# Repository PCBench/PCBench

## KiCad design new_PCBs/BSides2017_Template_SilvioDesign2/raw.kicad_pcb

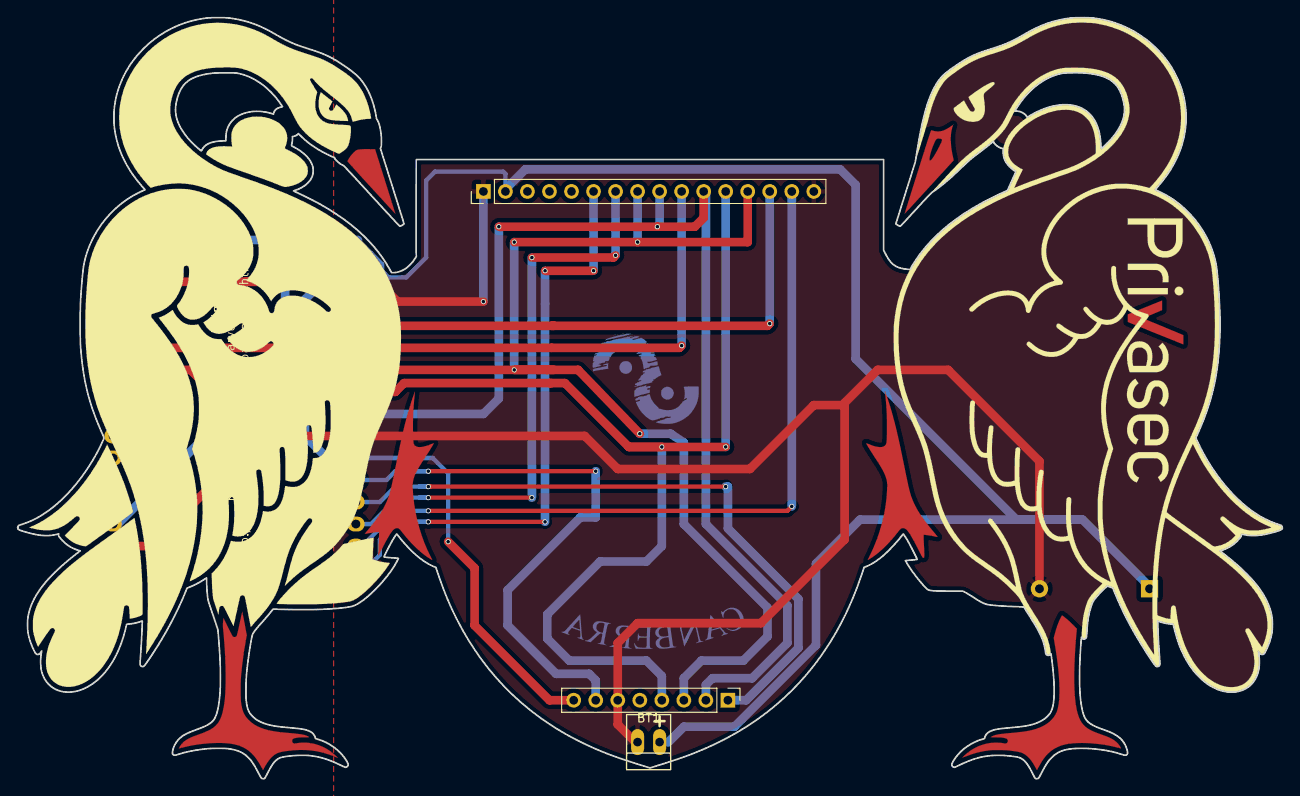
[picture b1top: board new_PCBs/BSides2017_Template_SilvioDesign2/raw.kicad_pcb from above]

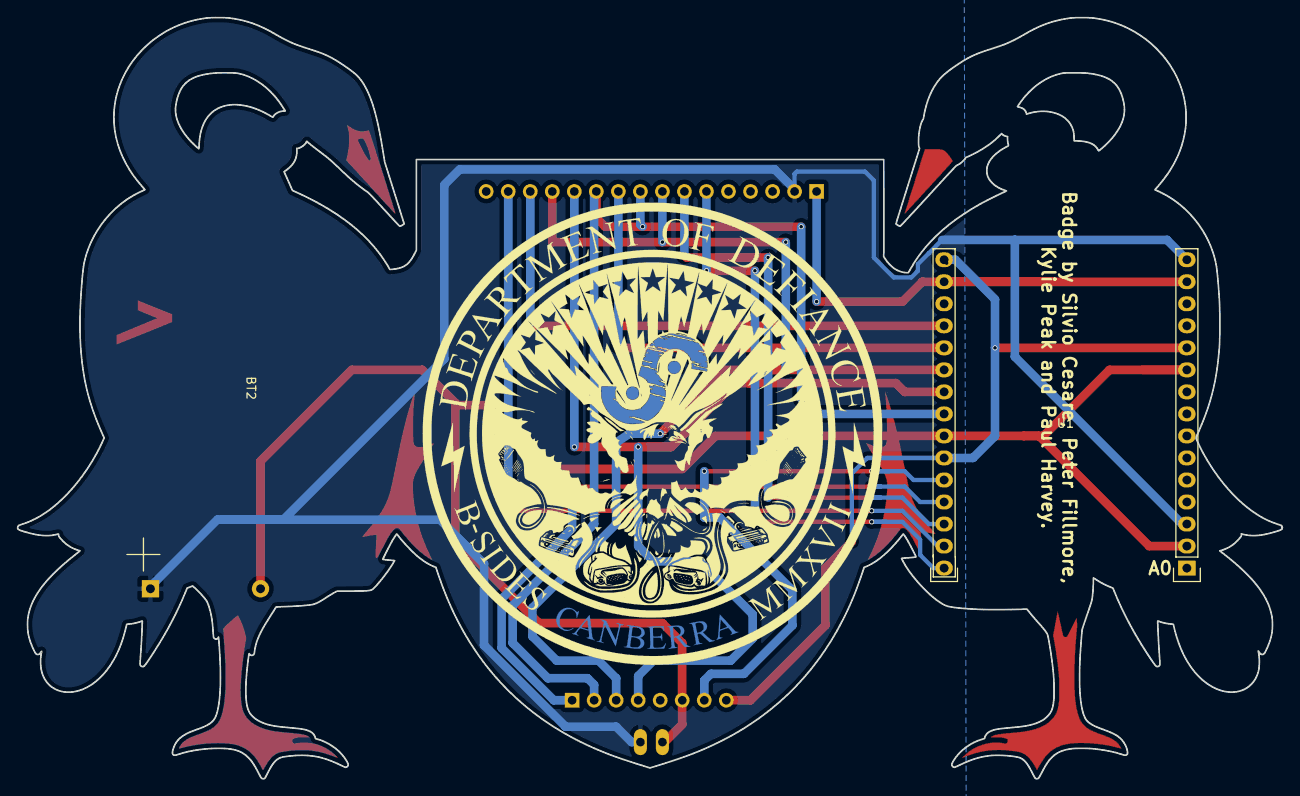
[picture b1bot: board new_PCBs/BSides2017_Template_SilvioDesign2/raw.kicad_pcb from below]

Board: 2 copper layers, 145.9 x 87.8 mm, 5 parts (2 on the bottom side), 13 nets.

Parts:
BT1: Battery; PINHEAD1-2
BT2: Battery; 2470_AAA_Battery_Holder
U1: NODEMCU_PART; NodeMCU_ThroughHole
U2: LCD_Display_Module_KMR18; Pin_Header_Straight_1x16_Pitch2.54mm
U3: RFID_READER; Pin_Header_Straight_1x08_Pitch2.54mm

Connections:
+3V3: U1.11, U1.16, U1.25, U3.8
GND: BT1.2, BT2.2, U1.2, U1.10, U1.14, U1.17, U1.24, U2.1, U2.16, U3.6
HCS: U1.20, U2.10
HMISO: U1.22, U2.12, U3.4
HMOSI: U1.21, U2.8, U2.13, U3.3
HSCLK: U1.23, U2.9, U2.11, U3.2
LCD_BACKLIGHT: U1.29, U2.15
LCD_DC_SELECT: U1.28, U2.7
LCD_RESET: U1.30, U2.6
RFID_RST_PIN: U1.26, U3.7
RFID_SS_PIN: U1.27, U3.1
SD_CS: U1.19, U2.14
VUSB: BT1.1, BT2.1, U1.3, U1.15, U2.2

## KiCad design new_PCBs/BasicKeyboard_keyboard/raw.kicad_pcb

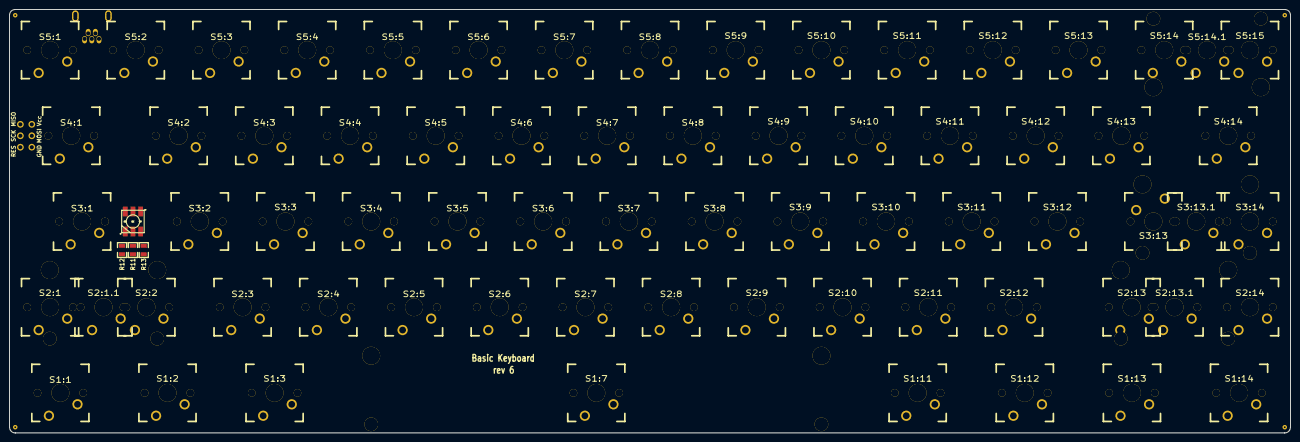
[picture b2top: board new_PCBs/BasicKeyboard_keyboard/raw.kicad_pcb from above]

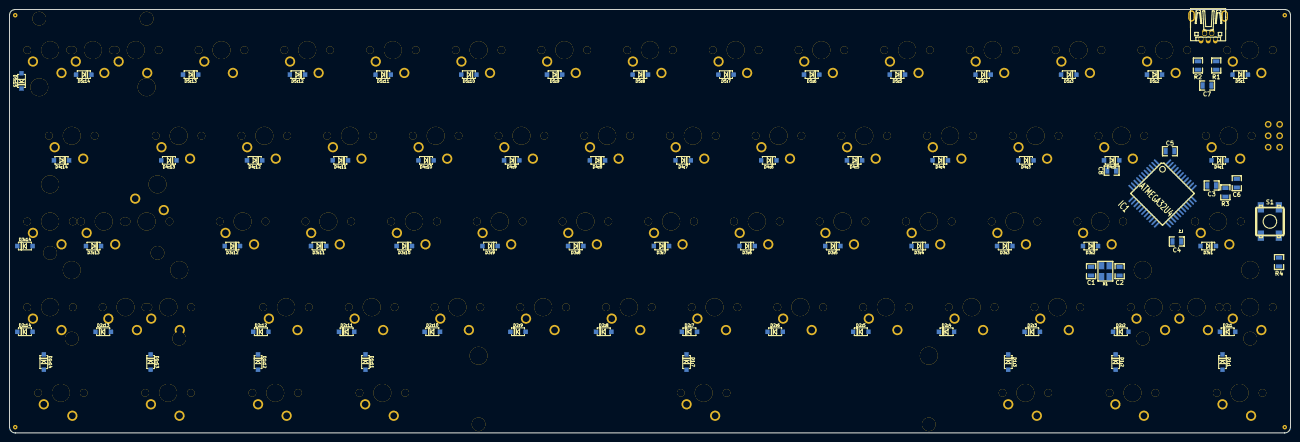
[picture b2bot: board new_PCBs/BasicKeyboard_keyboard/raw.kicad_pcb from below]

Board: 2 copper layers, 284.7 x 94.1 mm, 164 parts (85 on the bottom side), 105 nets, no tracks yet.

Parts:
C1, C2: 22pf; SM0805
C3, C4, C5, C6: 0.1uF; SM0805
C7, C8: 1uF; SM0805
D1:1, D1:2, D1:3, D1:7, D1:11, D1:12, D1:13, D1:14, D2:1, D2:2, D2:3, D2:4, D2:5, D2:6, D2:7, D2:8, D2:9, D2:10, D2:11, D2:12, D2:13, D2:14, D3:1, D3:2, D3:3, D3:4, D3:5, D3:6, D3:7, D3:8, D3:9, D3:10, D3:11, D3:12, D3:13, D3:14, D4:1, D4:2, D4:3, D4:4, D4:5, D4:6, D4:7, D4:8, D4:9, D4:10, D4:11, D4:12, D4:13, D4:14, D5:1, D5:2, D5:3, D5:4, D5:5, D5:6, D5:7, D5:8, D5:9, D5:10, D5:11, D5:12, D5:13, D5:14, D5:15: 1N4148; SOD-123
IC1: ATMEGA32U4; TQFP44
J1: USBMINI_B05; USB_MINI-B_MOLEX_54819-0519
L1: LED_SMD_RGB_5050; RGBLED5050
P1, P2, P3, P4: GND; Pad_Gnd
P5: MISO; Pad
P6: Vcc; Pad
P7: SCK; Pad
P8: MOSI; Pad
P9: RES; Pad
P10: GND; Pad
R1, R2: 22Ω; SM0805
R3, R4: 10kΩ; SM0805
R11: 100; SM0805
R12: 120; SM0805
R13: 150; SM0805
S1: ADTSMW69NVTR; ADTSJW65RV
S1:1, S1:2, S1:3, S1:11, S1:12, S1:13, S1:14, S2:2, S3:13: MX1A; CHERRY_PCB_125H_Visible
S1:7: MX1A; CHERRY_PCB_625H_Rev
S2:1, S2:3, S2:4, S2:5, S2:6, S2:7, S2:8, S2:9, S2:10, S2:11, S2:12, S2:14, S3:2, S3:3, S3:4, S3:5, S3:6, S3:7, S3:8, S3:9, S3:10, S3:11, S3:12, S3:14, S4:2, S4:3, S4:4, S4:5, S4:6, S4:7, S4:8, S4:9, S4:10, S4:11, S4:12, S4:13, S5:1, S5:2, S5:3, S5:4, S5:5, S5:6, S5:7, S5:8, S5:9, S5:10, S5:11, S5:12, S5:13, S5:14, S5:15: MX1A; CHERRY_PCB_100H_Plated
S2:1.1, S3:13.1: MX1A; CHERRY_PCB_225H_Visible
S2:13, S3:1: MX1A; CHERRY_PCB_175H_Visible
S2:13.1: MX1A; CHERRY_PCB_275H_Visible
S4:1, S4:14: MX1A; CHERRY_PCB_150H_Visible
S5:14.1: MX1A; CHERRY_PCB_200H_Visible_REV
X1: 7M-16.000MAAJ-T

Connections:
/MISO: IC1.11, P5.1
/MOSI: IC1.10, P8.1
/Matrix/col1: D1:1.2, D2:1.2, D3:1.2, D4:1.2, D5:1.2, IC1.18
/Matrix/col2: D1:2.2, D2:2.2, D3:2.2, D4:2.2, D5:2.2, IC1.19
/Matrix/col3: D1:3.2, D2:3.2, D3:3.2, D4:3.2, D5:3.2, IC1.20
/Matrix/col4: D2:4.2, D3:4.2, D4:4.2, D5:4.2, IC1.21
/Matrix/col5: D2:5.2, D3:5.2, D4:5.2, D5:5.2, IC1.25
/Matrix/col6: D2:6.2, D3:6.2, D4:6.2, D5:6.2, IC1.22
/Matrix/col7: D1:7.2, D2:7.2, D3:7.2, D4:7.2, D5:7.2, IC1.26
/Matrix/col8: D2:8.2, D3:8.2, D4:8.2, D5:8.2, IC1.27
/Matrix/col9: D2:9.2, D3:9.2, D4:9.2, D5:9.2, IC1.31
/Matrix/col10: D2:10.2, D3:10.2, D4:10.2, D5:10.2, IC1.32
/Matrix/col11: D1:11.2, D2:11.2, D3:11.2, D4:11.2, D5:11.2, IC1.41
/Matrix/col12: D1:12.2, D2:12.2, D3:12.2, D4:12.2, D5:12.2, IC1.40
/Matrix/col13: D1:13.2, D2:13.2, D3:13.2, D4:13.2, D5:13.2, IC1.39
/Matrix/col14: D1:14.2, D2:14.2, D3:14.2, D4:14.2, D5:14.2, IC1.38
/Matrix/col15: D5:15.2, IC1.37
/Matrix/row1: IC1.8, S1:1.1, S1:2.1, S1:3.1, S1:7.1, S1:11.1, S1:12.1, S1:13.1, S1:14.1
/Matrix/row2: S2:1.1, S2:1.1.1, S2:2.1, S2:3.1, S2:4.1, S2:5.1, S2:6.1, S2:7.1, S2:8.1, S2:9.1, S2:10.1, S2:11.1, S2:12.1, S2:13.1, S2:13.1.1, S2:14.1
/Matrix/row3: S3:1.1, S3:2.1, S3:3.1, S3:4.1, S3:5.1, S3:6.1, S3:7.1, S3:8.1, S3:9.1, S3:10.1, S3:11.1, S3:12.1, S3:13.1, S3:13.1.1, S3:14.1
/Matrix/row4: S4:1.1, S4:2.1, S4:3.1, S4:4.1, S4:5.1, S4:6.1, S4:7.1, S4:8.1, S4:9.1, S4:10.1, S4:11.1, S4:12.1, S4:13.1, S4:14.1
/Matrix/row5: IC1.28, S5:1.1, S5:2.1, S5:3.1, S5:4.1, S5:5.1, S5:7.1, S5:9.1, S5:10.1, S5:11.1, S5:12.1, S5:13.1, S5:14.1, S5:14.1.1, S5:15.1
/PWM1: IC1.29, R11.2
/PWM2: IC1.30, R13.2
/PWM3: IC1.12, R12.2
/SCK: IC1.9, P7.1
/~RES~: IC1.13, P9.1, R4.2, S1.4
GND: C1.2, C2.2, C3.2, C4.2, C5.2, C6.2, C7.2, C8.2, IC1.5, IC1.15, IC1.23, IC1.35, IC1.43, J1.5, L1.1, L1.2, L1.3, P1.1, P2.1, P3.1, P4.1, P10.1, R3.2, S1.2, X1.2, X1.4
unnamed: J1.3, R2.2
unnamed: J1.2, R1.2
unnamed: C2.1, IC1.17, X1.3
unnamed: IC1.4, R2.1
unnamed: L1.4, R12.1
unnamed: IC1.33, R3.1
unnamed: L1.6, R13.1
unnamed: L1.5, R11.1
unnamed: IC1.3, R1.1
unnamed: C8.1, IC1.6
unnamed: C1.1, IC1.16, X1.1
unnamed: D3:2.1, S3:2.2
unnamed: D3:1.1, S3:1.2
unnamed: D3:3.1, S3:3.2
unnamed: D3:4.1, S3:4.2
unnamed: D2:9.1, S2:9.2
unnamed: D2:10.1, S2:10.2
unnamed: D2:11.1, S2:11.2
unnamed: D2:14.1, S2:14.2
unnamed: D2:12.1, S2:12.2
unnamed: D3:11.1, S3:11.2
unnamed: D3:12.1, S3:12.2
unnamed: D3:14.1, S3:14.2
unnamed: D4:1.1, S4:1.2
unnamed: D3:6.1, S3:6.2
unnamed: D3:7.1, S3:7.2
unnamed: D3:5.1, S3:5.2
unnamed: D3:8.1, S3:8.2
unnamed: D3:9.1, S3:9.2
unnamed: D3:10.1, S3:10.2
unnamed: D1:2.1, S1:2.2
unnamed: D1:3.1, S1:3.2
unnamed: D5:15.1, S5:15.2
unnamed: D1:11.1, S1:11.2
unnamed: D2:4.1, S2:4.2
unnamed: D2:5.1, S2:5.2
unnamed: D2:6.1, S2:6.2
unnamed: D2:7.1, S2:7.2
unnamed: D2:8.1, S2:8.2
unnamed: D1:12.1, S1:12.2
unnamed: D1:14.1, S1:14.2
unnamed: D2:2.1, S2:2.2
unnamed: D2:3.1, S2:3.2
unnamed: D5:6.1, S5:6.2
unnamed: D5:8.1, S5:8.2
unnamed: D5:9.1, S5:9.2
unnamed: D5:10.1, S5:10.2
unnamed: D5:11.1, S5:11.2
unnamed: D5:12.1, S5:12.2
unnamed: D5:13.1, S5:13.2
unnamed: D2:13.1, S2:13.2, S2:13.1.2
unnamed: D2:1.1, S2:1.2, S2:1.1.2
unnamed: D3:13.1, S3:13.2, S3:13.1.2
unnamed: D5:14.1, S5:14.2, S5:14.1.2
unnamed: D1:7.1, S1:7.2
unnamed: D1:13.1, S1:13.2
unnamed: D4:8.1, S4:8.2
unnamed: D4:9.1, S4:9.2
unnamed: D4:7.1, S4:7.2
unnamed: D4:10.1, S4:10.2
unnamed: D4:11.1, S4:11.2
unnamed: D4:2.1, S4:2.2
unnamed: D4:3.1, S4:3.2
unnamed: D4:4.1, S4:4.2
unnamed: D4:12.1, S4:12.2
unnamed: D4:5.1, S4:5.2
unnamed: D4:6.1, S4:6.2
unnamed: D5:4.1, S5:4.2
unnamed: D5:5.1, S5:5.2
unnamed: D5:7.1, S5:7.2
unnamed: D4:13.1, S4:13.2
unnamed: D4:14.1, S4:14.2
unnamed: D5:1.1, S5:1.2
unnamed: D5:2.1, S5:2.2
unnamed: D5:3.1, S5:3.2
unnamed: D1:1.1, S1:1.2
VCC: C3.1, C4.1, C5.1, C6.1, C7.1, IC1.2, IC1.7, IC1.14, IC1.24, IC1.34, IC1.44, J1.1, P6.1, R4.1

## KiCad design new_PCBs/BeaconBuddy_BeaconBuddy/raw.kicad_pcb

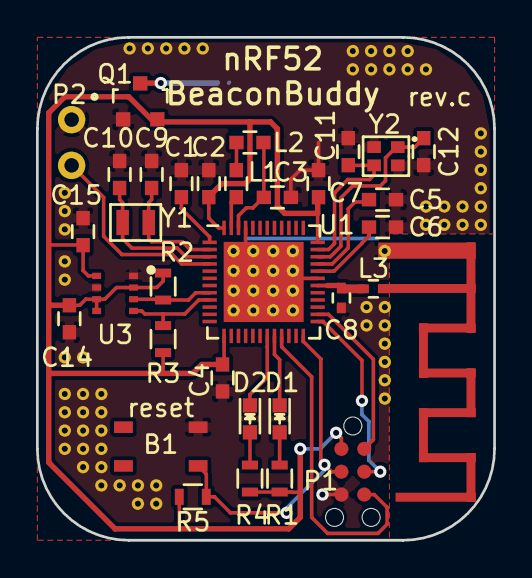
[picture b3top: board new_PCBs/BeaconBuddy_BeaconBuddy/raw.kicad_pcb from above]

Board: 2 copper layers, 25.4 x 27.9 mm, 34 parts (1 on the bottom side), 26 nets.

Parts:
A1: Antenna; Antenna-2.45GHZ
B1: SKRPABE010
BT1: BAT-HLD-001; BATT-HLD-001
C1, C4, C7, C14, C15: 0.1uF; C_0603
C2: 4.7uF; C_0603
C3: 1uF; C_0603
C5: 100pF; C_0603
C6: NC; C_0603
C8: 0.8pF; C_0402
C9, C10, C11, C12: 12pF; C_0603
D1: L0603G; LED_0603
D2: L0603R; LED_0603
L1: 10uH; C_0603
L2: 15nH; C_0603
L3: 3.9nH; C_0402
P1: CONN_01X06; TC2030-MCP-NL
P2: AIN0; CONN_100mil_1x2
Q1: Si2365EDS; SOT-23
R1, R4: 470; R_0603
R2, R3: 4.7k; R_0603
R5: 10k; R_0603
U1: nRF52832-QFAA; UQFN-48-1EP_6x6mm_Pitch0.4mm
U3: BME280; Bosch_LGA8_2.5x2.5
Y1: 32.768kHz; Crystal_ABS06
Y2: 32MHz; Crystal_ABM11

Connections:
/AIN0: P2.2, U1.4
/ANT: C8.1, L3.2, U1.30
/RF_OUT: A1.1, L3.1
/SCL: R3.2, U1.9, U3.4
/SDA: R2.2, U1.8, U3.3
/SWDCLK: P1.4, U1.25
/SWDIO: P1.2, U1.26
/SWO: P1.6, U1.21
/XC1: C11.2, U1.35, Y2.3
/XC2: C12.2, U1.34, Y2.1
/XL1: C9.2, U1.2, Y1.1
/XL2: C10.2, U1.3, Y1.2
/nRESET: B1.1, P1.3, R5.2, U1.24
GND: A1.2, B1.3, BT1.2, C1.2, C2.2, C3.2, C4.2, C5.1, C6.1, C7.2, C8.2, C9.1, C10.1, C11.1, C12.1, C14.2, C15.2, P1.5, P2.1, Q1.1, U1.31, U1.45, U1.49, U3.1, U3.7, Y2.2, Y2.4
unnamed: BT1.1, Q1.3
unnamed: C1.1, U1.1
unnamed: C3.1, L2.1, U1.46
unnamed: C5.2, U1.33
unnamed: C6.2, U1.32
unnamed: D1.1, U1.20
unnamed: D1.2, R1.1
unnamed: D2.1, U1.19
unnamed: D2.2, R4.1
unnamed: L1.1, L2.2
unnamed: L1.2, U1.47
VDD: C2.1, C4.1, C7.1, C14.1, C15.1, P1.1, Q1.2, R1.2, R2.1, R3.1, R4.2, R5.1, U1.13, U1.36, U1.48, U3.2, U3.5, U3.6, U3.8

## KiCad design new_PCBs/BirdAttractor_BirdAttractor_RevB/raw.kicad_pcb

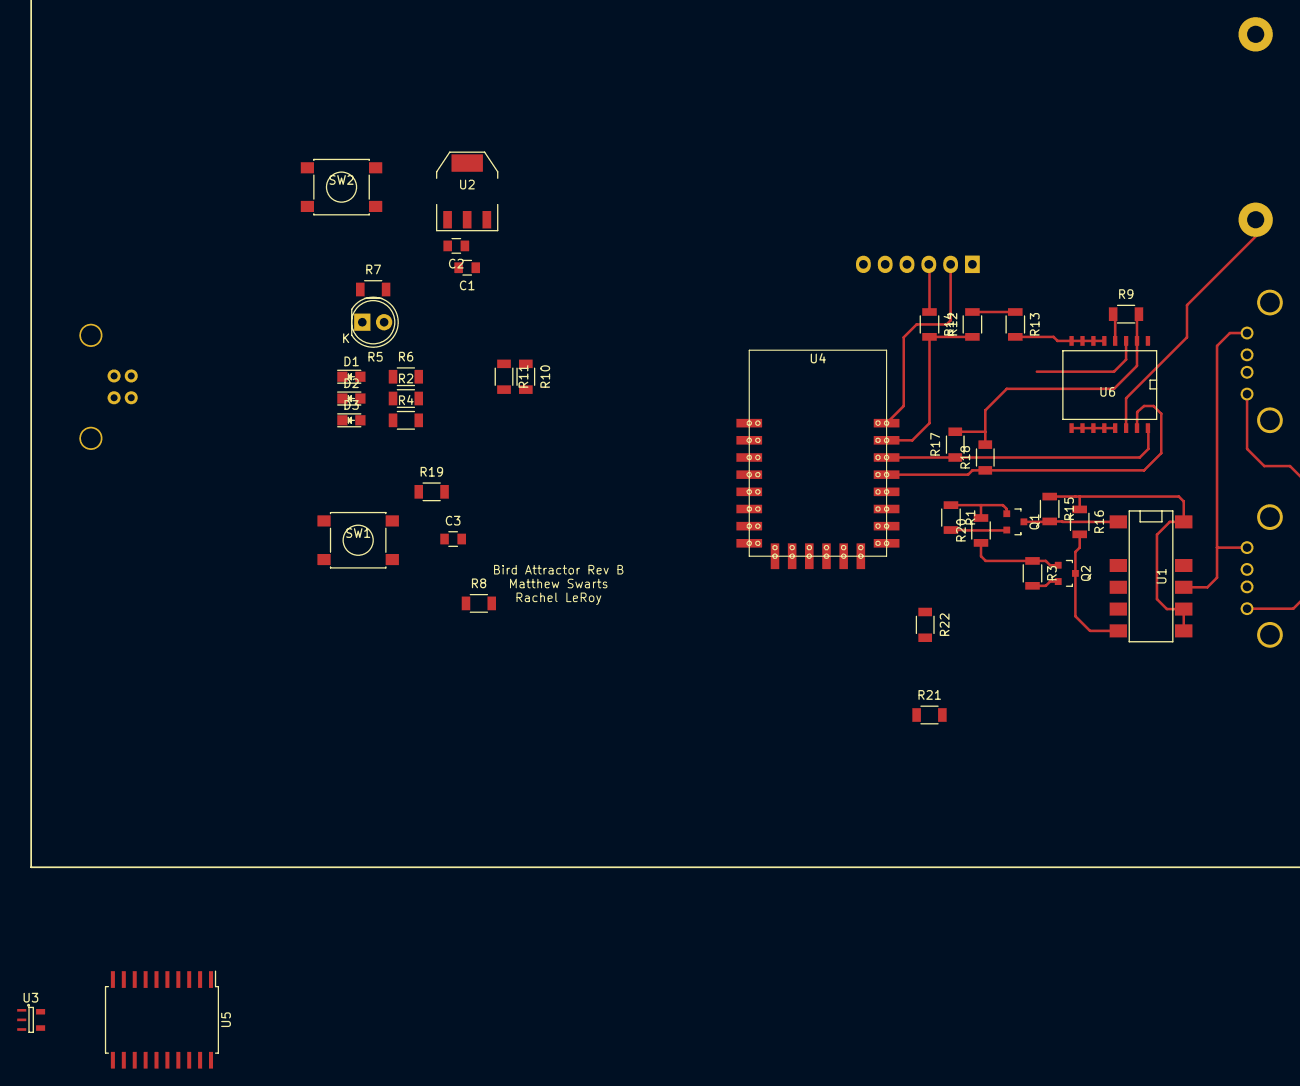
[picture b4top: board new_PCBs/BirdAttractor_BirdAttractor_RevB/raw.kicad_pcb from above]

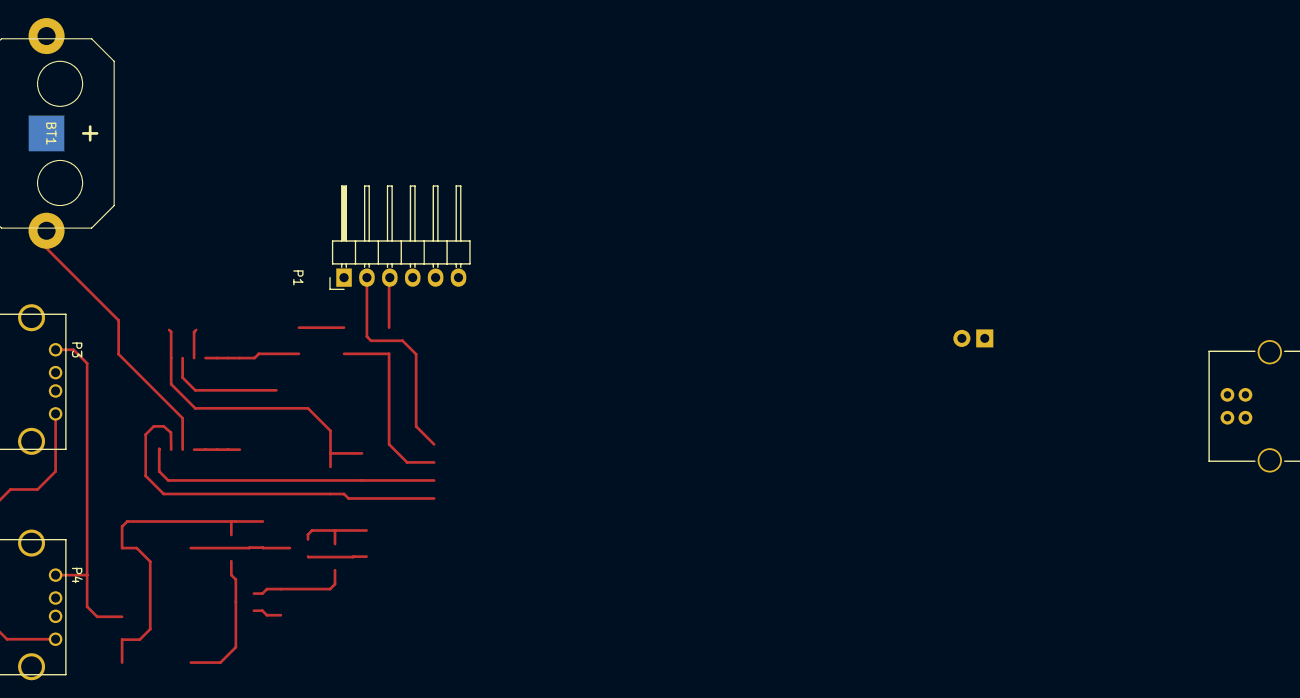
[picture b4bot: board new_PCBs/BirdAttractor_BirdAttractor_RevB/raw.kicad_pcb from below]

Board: 2 copper layers, 43 parts (5 on the bottom side), 30 nets.

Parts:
BT1: 3V Battery; BK-913
C1: 1uF; C_0805
C2: 10uF; C_0805
C3: 0.1uF; C_0805
D1, D2, D3: LED; LED-0805
P1: FTDI; Pin_Header_Angled_1x06
P2: USB_B
P3, P4: USB_A
Q1, Q2: BSS138; SOT-23
R1, R3, R12, R13, R15, R16: 10K; R_1206
R2, R4: 68; C_1206
R5: Photores; LED-5MM
R6: 18; C_1206
R7, R19: 1K; C_1206
R8: 2.7K; C_1206
R9: 100K; C_1206
R10, R11, R21, R22: 10K; C_1206
R14: 10K/0; R_1206
R17, R18: 47K; C_1206
R20: 0; R_1206
SW1, SW2: SW_PUSH; SW_SPST_PTS645
U1: PR_Relay_V23079; DIP-12-SMD
U2: AMS1117-3.3; SOT-223
U3: SN74LVC1G14; SOT-23-5-80
U4: ESP8266-12E; ESP8266-12E-80
U5: PCF2129AT; SOIC-20_7.5x12.8mm_Pitch1.27mm-80
U6: DS3231; SO-16-W

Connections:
5V_IN: C1.1, P1.4, P2.1, R15.1, R16.1, U1.7, U1.8, U1.12, U2.3
5V_OUT: P3.1, P4.1, U1.9
ADC: R5.2, R7.2, U4.2
ALARM_WAKE: C3.1, R8.1, R11.2, R19.2, U4.1, U6.3
CH_PD: R10.1, U4.3
DEEP_SLEEP_WAKE: R8.2, U4.4
GND: BT1.2, C1.2, C2.2, C3.2, D1.1, D2.1, D3.1, P1.6, P2.4, P3.4, P4.4, R7.1, R13.2, R22.2, SW1.2, SW2.2, U2.1, U4.15, U6.5, U6.6, U6.7, U6.8, U6.9, U6.10, U6.11, U6.12, U6.13
LED_5V_IN: R2.2, U4.6
LED_5V_OUT: R4.2, U4.7
LED_WIFI: R6.2, U4.5
unnamed: D1.2, R6.1
unnamed: D2.2, R2.1
unnamed: D3.2, R4.1
unnamed: R9.1, U6.4
unnamed: R12.2, R13.1
unnamed: R19.1, SW1.1
unnamed: R21.1, U4.17
unnamed: R22.1, U4.16
PROGRAM: SW2.1, U4.18
RELAY_OFF: Q1.3, R15.2, U1.1
RELAY_OFF33: Q1.2, R1.2, U4.12
RELAY_ON: Q2.3, R16.2, U1.6
RELAY_ON33: Q2.2, R3.2, U4.11
RX: P1.3, R14.1
RX33: R12.1, R14.2, U4.21
SCL: R17.1, U4.20, U6.16
SDA: R18.1, U4.19, U6.15
TX: P1.2, U4.22
V33: C2.1, Q1.1, Q2.1, R1.1, R3.1, R5.1, R9.2, R10.2, R11.1, R17.2, R18.2, R20.1, R20.2, R21.2, U2.2, U4.8, U6.2
VBAT: BT1.1, U6.14

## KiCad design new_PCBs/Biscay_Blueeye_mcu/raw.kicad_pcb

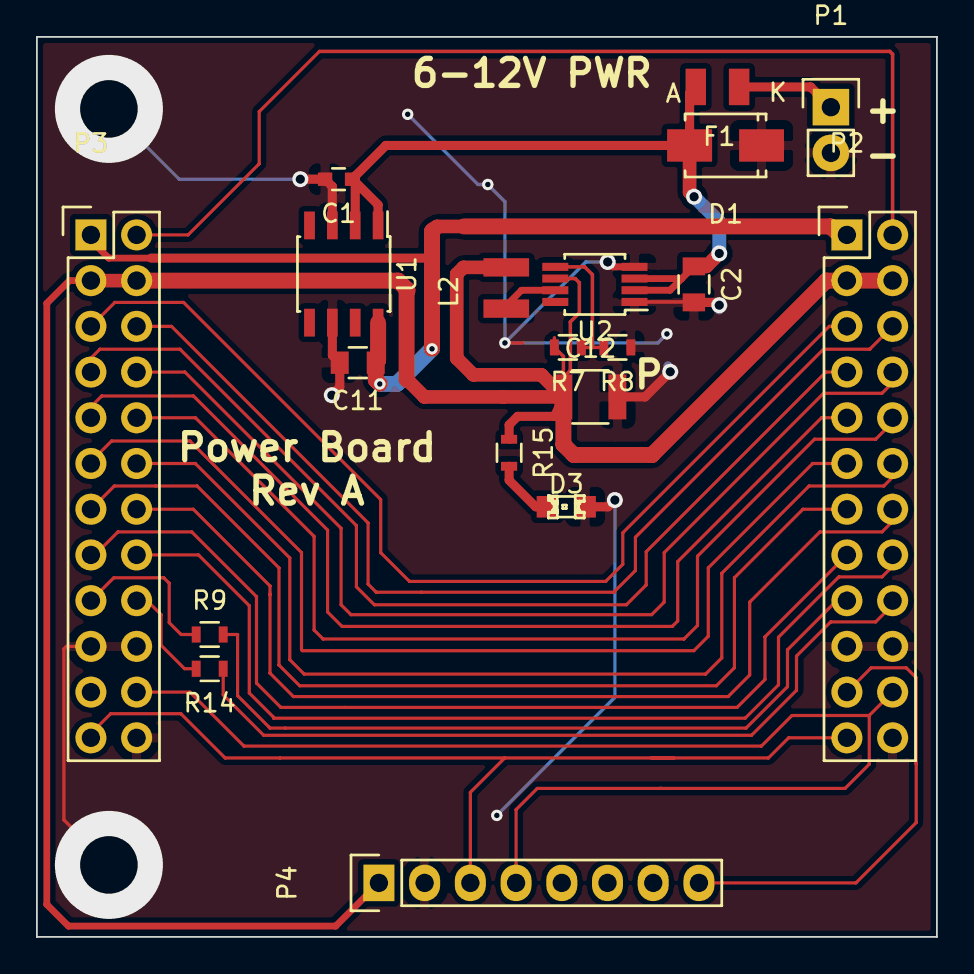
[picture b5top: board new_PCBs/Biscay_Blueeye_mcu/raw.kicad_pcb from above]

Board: 2 copper layers, 50.0 x 50.0 mm, 19 parts (0 on the bottom side), 28 nets.

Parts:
C1: 1u; C_0603
C2: 10u; C_0805
C11: 4.7u; C_0805
C12: 22u; C_1210
D1: >2A; Diode-SMA_Standard
D3: GREEN; LED-0805
F1: 2A poly; Fuse_SMD1206_Reflow
L2: VLF252015MT-2R2M; Neosid_Inductor_SM-NE29_SMD1008
P1: 6V PWR; Pin_Header_Straight_1x02
P2, P3: FPGA; Pin_Header_Straight_2x12
P4: MPU9150; Pin_Header_Straight_1x08
R7: 715k; R_0603
R8: 180k; R_0603
R9, R14: 10k; R_0603
R15: 330; R_0603
U1: LK115D50; SOIC-8_3.9x4.9mm_Pitch1.27mm
U2: TPS62160; MSOP-8_3x3mm_Pitch0.65mm

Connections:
+3V3: C12.1, L2.2, P2.3, P2.4, P3.3, P3.4, P4.1, R7.2, R15.1, U2.6
+5V: C11.1, P2.1, P3.1, U1.8
+BATT: C1.1, C2.1, D1.2, F1.2, U1.1, U1.2, U2.2, U2.3
/ACC_INT: P2.21, P4.8
/CAPTD: P2.10, P3.10
/CLR: P2.11, P3.11
/DAC_MOSI: P2.13, P3.13
/DAC_SCLK: P2.14, P3.14
/DAC_~SYNC: P2.15, P3.15
/FPGA_MISO: P2.8, P3.8
/FPGA_MOSI: P2.7, P3.7
/FPGA_SCK: P2.5, P3.5
/FPGA_SCL: P2.23, P3.23, P4.3
/FPGA_SDA: P2.22, P3.22, P4.4
/FPGA_~CS0: P2.6, P3.6
/FPGA_~CS1: P2.12, P3.12
/MON_5VA: P2.2, P3.2
/REG_EN: P2.16, P3.16
/TEMPS: P2.18, R14.1
/TRIGD: P2.9, P3.9
/Vb_MON: P2.17, R9.2
GND: C1.2, C2.2, C11.2, C12.2, D1.1, D3.2, P1.2, P2.19, P2.20, P2.24, P3.19, P3.20, P3.24, P4.2, R8.1, U1.3, U1.6, U2.1, U2.4
unnamed: D3.1, R15.2
unnamed: F1.1, P1.1
unnamed: L2.1, U2.7
unnamed: P3.17, R9.1
unnamed: P3.18, R14.2
unnamed: R7.1, R8.2, U2.5

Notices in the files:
new_PCBs/BirdAttractor_BirdAttractor_RevB/raw.kicad_pcb:
MIT License
